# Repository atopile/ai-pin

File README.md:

## AI Pin — Your private, wearable memory

**Stop forgetting what matters.** AI Pin is a privacy‑first wearable that captures your conversations throughout the day, then—when you’re home—offloads to your own local server to transcribe and make everything searchable. Ask, “What did I promise Alex yesterday?” or “What did I get done today?” and get instant answers from your own life.

### Why this is different

- **AI‑designed hardware**: The PCB is designed using `atopile` (a declarative electronics DSL) and lives as code in `ai-pin.ato`.
- **Local‑first by default**: All storage, transcription, embeddings and search run on your own machine—no cloud or third‑party services.
- **End‑to‑end system**: Wearable capture → local ingestion → Whisper transcription → vector search → Q&A and daily summaries.

### What it does

- **Continuous or on‑demand capture** via an I2S MEMS mic, storing audio on microSD.
- **Nightly offload** over Wi‑Fi while charging to a local server (Docker Compose).
- **Local transcription** using Whisper (GPU if available, CPU fallback).
- **Search & recall** across transcripts with semantic + keyword search.
- **Daily digest** of your day’s conversations and key moments.

### Moments you’ll stop forgetting

- “What did I promise to follow up on in today’s meeting?”
- “Who did I meet at the event—and what did we agree to do next?”
- “Which book/podcast did Sam recommend at lunch?”
- “What were the price, dates, and address the contractor mentioned?”
- “Where did we leave off on that debugging thread last week?”
- “What did the coach say about pickup changes for tomorrow?”
- “What’s the Wi‑Fi password/door code they told me?”
- “What exact phrasing did I use when I committed to that deliverable?”
- “What were the three ideas I said I’d write down later?”

---

## Architecture

```mermaid
graph TD
  Wearable["ESP32‑C3 AI Pin<br/>I2S mic → microSD (WAV)"] -->|Wi‑Fi offload| API[FastAPI Ingestion]
  API --> MINIO[(MinIO Object Storage)]
  API --> REDIS[(Redis Queue)]
  REDIS --> WORKER[Whisper Worker]
  MINIO --> WORKER
  WORKER --> MINIO
  WORKER --> DB[(Postgres + pgvector)]
  UI[Search & Daily Digest UI] --> API
  API --> DB
```

### Processing flow (upload → answer)

```mermaid
sequenceDiagram
    participant Dev as Device
    participant API as Ingestion API
    participant S3 as MinIO
    participant Q as Redis Queue
    participant W as Whisper Worker
    participant DB as Postgres/pgvector

    Dev->>API: POST /v1/upload (WAV)
    API->>S3: putObject(wav)
    API->>Q: enqueue({ key, device_id })
    W-->>Q: blpop()
    Q-->>W: { key, device_id }
    W->>S3: getObject(wav)
    W->>W: transcribe (Whisper)
    W->>S3: putObject(txt/json)
    W->>DB: upsert chunks + embeddings
    Note over W,DB: hybrid index: BM25 + vector
    UI->>API: /v1/search?q=...&time=...
    API->>DB: retrieve + rank
    API-->>UI: results/snippets
```

### Hardware (designed in code)

- MCU: ESP32‑C3 Mini‑1 (`I2S`, `SPI`, `Wi‑Fi`)
- Mic: TDK InvenSense ICS‑43434 (digital I2S)
- Storage: microSD over SPI
- Power: USB‑C → BQ25185 charger/power‑path → LDO (3.3 V)
- Battery: LP402535 (configurable)

See `ai-pin.ato` for the complete, declarative hardware design.

### Firmware (Zephyr RTOS)

- I2S capture → ring buffer → WAV writer (5–10 min segments)
- FATFS on SPI microSD, crash‑safe finalize, sidecar metadata
- Wi‑Fi offload window while charging; TLS upload
- Simple UX: LED states and a single button

### Local backend (Docker Compose)

- Ingestion API (FastAPI)
- Object storage (MinIO)
- Database (Postgres + pgvector)
- Queue (Redis)
- Transcription worker (Whisper via `faster-whisper`)

---

## Agents and your private history

You can point a local agent at your private transcripts to answer questions and automate tasks—without sending data to the cloud.

- **Local‑only by default**: Retrieval happens against your local DB/object store. No outbound calls unless you enable them.
- **Hybrid retrieval**: BM25 + vector search with time filters and device/user scoping.
- **Defensive prompts**: The API returns citations and timestamps; agents are encouraged to include them in answers.

Planned Agent API (local):

- `GET /v1/search` – hybrid search over transcripts
- `POST /v1/agents/query` – higher‑level query that returns stitched context windows for LLMs
- `POST /v1/agents/sessions` – create a scoped session with time/person/topic constraints

Example (planned) search call:

```bash
curl "http://localhost:8080/v1/search?q=what+did+I+promise+Alex&from=2025-01-01&to=2025-01-31&top_k=10"
```

Privacy boundaries:

- Local network only; bind to loopback or LAN per your `.env`.
- API tokens for agent clients; optional mTLS.
- Audit log of queries; per‑user/device scoping.
- Optional redaction layer (emails, credit cards) before indexing.

---

## Quickstart

### 1) Start the local stack

Create `backend/compose/.env` with these defaults (edit as needed):

```env
API_HOST=0.0.0.0
API_PORT=8080

MINIO_ENDPOINT=minio:9000
MINIO_ACCESS_KEY=minio
MINIO_SECRET_KEY=minio12345
MINIO_SECURE=false
MINIO_BUCKET=aipin

REDIS_URL=redis://redis:6379/0
WHISPER_MODEL=small
WHISPER_COMPUTE_TYPE=auto
```

Then launch:

```bash
cd backend/compose
docker compose up -d
```

Services:

- API: `http://localhost:8080`
- MinIO console: `http://localhost:9001` (user: `minio`, pass: `minio12345`)
- Postgres: `localhost:5432`
- Redis: `localhost:6379`

Health check:

```bash
curl http://localhost:8080/healthz
```

### 2) Upload a sample WAV (simulating the device)

```bash
curl -X POST \
  -F "device_id=test-device" \
  -F "file=@/path/to/sample.wav;type=audio/wav" \
  http://localhost:8080/v1/upload
```

The worker will pick it up, transcribe, and write a `.txt` next to the `.wav` in MinIO.

---

## Developing the firmware (ESP32‑C3 + Zephyr)

See detailed instructions in `firmware/zephyr/README.md`. Quickstart:

Prereqs (one‑time):

```bash
/opt/homebrew/bin/python3 -m venv "$HOME/zephyr-venv"
source "$HOME/zephyr-venv/bin/activate"
pip install -U pip west
cd "$HOME/zephyrproject"
export ZEPHYR_SDK_INSTALL_DIR="$HOME/zephyr-sdk-0.17.2"
export ZEPHYR_TOOLCHAIN_VARIANT=zephyr
west zephyr-export
```

Build & flash:

```bash
source "$HOME/zephyr-venv/bin/activate"
cd "$HOME/zephyrproject"
west build -b esp32c3_devkitm $(pwd -P)/../projects/ai-pin/firmware/zephyr/app -p always -- \
  -DDTC_OVERLAY_FILE=boards/esp32c3_devkitm.overlay \
  -DPython3_EXECUTABLE="$HOME/zephyr-venv/bin/python" -DWEST_PYTHON="$HOME/zephyr-venv/bin/python"
west flash
```

Provision Wi‑Fi on SD card (root):

```ini
ssid=YOUR_SSID
psk=YOUR_PASSWORD
```

Troubleshooting highlights:

- Missing blobs for ESP32: `west blobs fetch hal_espressif`
- I2S DMA error: ensure overlay enables `&dma { status = "okay"; }` and `&i2s { dmas = <&dma 0>, <&dma 1>; }`, and `CONFIG_DMA=y` in `prj.conf`
- CMake can’t find west: pass venv python flags shown above

---

## Project status

- Hardware captured in `ai-pin.ato` (Atopile)
- Backend Compose stack scaffolded: API + MinIO + Postgres + Redis + Whisper worker
- Firmware stubs prepared (Zephyr app structure)

See `spec.md` and `todo.md` for detailed scope, milestones, and open questions.

---

## Roadmap (MVP highlights)

- End‑to‑end ingest → transcribe
- Daily summary generation
- OTA updates via MCUboot
- Optional SD encryption and mTLS device identity

---

## Contributing

Issues and PRs welcome. The goal is a great local‑first reference design for private, wearable memory.

---

## License

MIT

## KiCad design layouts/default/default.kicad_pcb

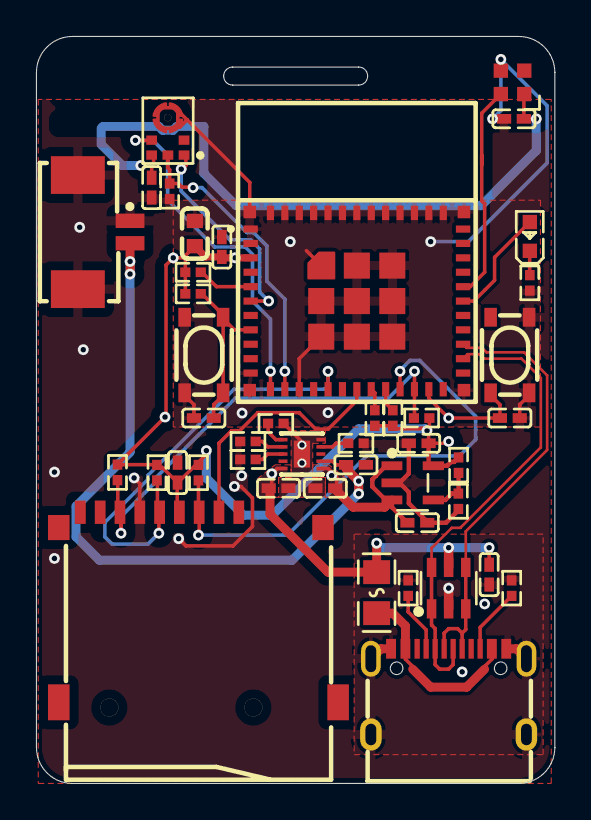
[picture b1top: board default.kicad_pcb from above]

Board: 2 copper layers, 28.8 x 41.5 mm, 46 parts (1 on the bottom side), 31 nets.

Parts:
B1: EEMB_BATTERY_LP402535
C1, C2, C9, C11: 1µF ±10% 25V X5R; C0402
C3, C4, C6, C7, C8, C12, C13: 100nF ±10% 16V X7R; C0402
C5: 22µF ±20% 6.3V X5R; C0603
C10: 10µF ±20% 6.3V X5R; C0402
Card1: TF-SMD_TF-01A
D1: SOT-23-6_L2.9-W1.6-P0.95-LS2.8-BL
F1: F0805
LED1: LED-SMD_4P-L2.0-W2.0-BR
LED3: LED0603-RD
LOGO1: atopile_Logo_4x4mm
R1, R2, R3, R5, R6, R7, R11, R12, R14, R15, R16, R17, R19: 10kΩ ±1% 62.5mW; R0402
R4: 16kΩ ±1% 62.5mW; R0402
R8: 100kΩ ±1% 62.5mW; R0402
R9, R10: 5.1kΩ ±1% 62.5mW; R0402
R13: 18kΩ ±1% 62.5mW; R0402
SW1, SW2: KEY-SMD_4P-L4.2-W3.2-P2.20-LS4.6
U1: SOT-23-5_L3.0-W1.7-P0.95-LS2.8-BL
U2: WIFIM-SMD_ESP32-C3-MINI-1
U3: MIC-SMD_6P-L3.5-W2.7-P0.90-BL
U4: CONN-SMD_532610271
U5: WSON-10_L2.2-W2.0-P0.40-BL-EP_TI_DLH0010A
USB1: USB-C-SMD_TYPE-C-6PIN-2MD-073

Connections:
-hv-0: C9.1, U4.2, U5.2
-hv-1: C8.1, C11.1, D1.5, F1.2, U5.10
-line-0: LED1.4, U2.31
-line-1: R1.2, U2.19
-line-2: R2.2, U2.20
-line-3: U2.12, U3.4
-line-4: R8.1, U2.13, U3.6
-line-5: U2.6, U3.1
ADJ_NC: R3.1, R4.2, U1.4
GND: Card1.10, Card1.11, Card1.12, Card1.13
ILIM_VSET: R13.1, U5.7
ISET: R11.1, U5.8
SYS: C1.1, C10.1, U1.1, U1.3, U5.1
TS_MR: R17.1, U5.6
anode: LED3.2, U2.30
cathode: LED3.1, R19.1
gnd: C1.2, C2.2, C3.1, C4.1, C5.2, C6.2, C7.2, C8.2, C9.2, C10.2, C11.2, C12.2, C13.2, Card1.6, D1.2, LED1.3, R3.2, R8.2, R9.2, R10.2, R11.2, R12.2, R13.2, R17.2, R19.2, SW1.1, SW1.2, SW2.1, SW2.2, U1.2, U2.1, U2.2, U2.11, U2.14, U2.36, U2.37, U2.38, U2.39, U2.40, U2.41, U2.42, U2.43, U2.44, U2.45, U2.46, U2.47, U2.48, U2.49, U2.50, U2.51, U2.52, U2.53, U3.3, U4.1, U4.3, U4.4, U5.5, U5.11, USB1.1, USB1.12, USB1.13, USB1.14, USB1.15, USB1.16
hv-0: F1.1, USB1.2, USB1.11
hv-1: C2.1, C5.1, C6.1, C7.1, C12.1, C13.1, Card1.4, LED1.1, R1.1, R2.1, R4.1, R5.2, R6.2, R7.1, R14.2, R15.2, R16.2, U1.5, U2.3, U3.5
line-0: R9.1, USB1.4
line-1: R10.1, USB1.10
line-4: D1.1, D1.6, U2.26, USB1.5, USB1.7
line-5: D1.3, D1.4, U2.27, USB1.6, USB1.8
mcu-line: R5.1, U2.5
nCE: R12.1, U5.4
output-0: C3.2, SW1.3, SW1.4, U2.23
output-1: C4.2, R7.2, SW2.3, SW2.4, U2.8
sd_chip_select_1: Card1.2, U2.18
sd_clk: Card1.5, R16.1, U2.16
sd_miso: Card1.7, R6.1, R14.1, U2.22
sd_mosi: Card1.3, R15.1, U2.21

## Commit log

2025-08-10 gpt5 building
2025-08-10 layout done
2025-08-10 add nice logo
2025-08-10 fix add usb comms connection
2025-08-11 feat: add backend API, whisper worker, and Zephyr firmware; docs updates; ato tooling config
2025-08-11 looking good
2025-08-11 chore: commit all pending changes
2025-08-11 chore: remove accidental audio file "borne & Alexis B - Hush.mp3"
2025-08-11 cleaning up readme
2025-08-23 firmware progress?
2025-08-23 got bitbang addressable, some clock issue
2025-08-30 ws2812 as nice as its going to get for now, moving on, rgb works
